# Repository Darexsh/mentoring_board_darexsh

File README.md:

* * *

<div align="center">

🧩 ESP32-S3 Mentoring Board
==========================

**A multi-function mentoring/training board with ESP32-S3, common sensors, inputs, and LEDs**  
🧠🛠️🎛️💡📦

<sub>Check out my bot in Telegram for an easy project overview.<br>If you want to support more projects, you can leave a small donation for a coffee.</sub>

</div>

* * *

✨ Authors
---------

| Name | GitHub | Role | Contact | Contributions |
| --- | --- | --- | --- | --- |
| **[Darexsh by Daniel Sichler](https://github.com/Darexsh)** | [Link](https://github.com/Darexsh?tab=repositories) | Hardware & Firmware Development 🖥️🛠️ | 📧 [E-Mail](mailto:sichler.daniel@gmail.com) | Concept, Hardware, Firmware, Board Bring-up |

* * *

🚀 About the Project
--------------------

This project is a **mentoring/training board** based on the ESP32-S3 microcontroller. It combines common sensors, inputs, LEDs, and storage so embedded features can be demonstrated and tested on a single board.

### 🛠️ Technologies

* **Microcontroller:** ESP32-S3-WROOM-1-N8R8  
* **Sensors:** VCNL4040 (ambient light & proximity), SHT4x (temperature & humidity), BNO085 (IMU), ADS1015 (ADC)  
* **Inputs:** push buttons, tactile switches, potentiometers, joystick, rotary encoder  
* **Outputs:** WS2812B-2020 addressable LEDs  
* **Storage:** microSD card (SPI)  
* **Display:** I2C display header  
* **Software:** C++, Arduino framework (PlatformIO)  
* **Tools:** KiCad, PlatformIO, Git  

* * *

📋 Features
===========

* **🧭 Sensor Demonstrations:** IMU, proximity/light, temperature/humidity, external ADC  
* **🎛️ Input Practice:** buttons, tactile switches, potentiometers, joystick, encoder  
* **💡 LED Control:** WS2812B addressable LEDs  
* **📦 Data Logging:** microSD over SPI  
* **🖥️ Optional I2C Display:** header for showing sensor values  
* **🧩 Modular Firmware:** enable features via compile-time flags  

* * *

🔧 Hardware Setup
-----------------

* **ESP32-S3 module**  
* **VCNL4040, SHT4x, BNO085, ADS1015** on I2C  
* **WS2812B-2020 LED chain**  
* **microSD socket** over SPI  
* **Joystick, potentiometers, buttons, encoder** for user input  
* **I2C display connector**  

* * *

🚀 Installation & Usage
-----------------------

1. Open the KiCad project in `Hardware/` if you want to inspect or modify the hardware.  
2. Build and flash the firmware with PlatformIO:  
   
   ```bash
   cd Software
   pio run -t upload
   pio device monitor
   ```
3. Enable/disable features in `Software/lib/select_sensory/select_sensory.h`.  

* * *

## 📜 License

This project is licensed under the **MIT License**.

This license applies to the updater application code in this repository. Upstream patch and app projects remain under their own licenses and notice terms.

**Copyright (c) 2025 Darexsh by Daniel Sichler**

You are free to use, copy, modify, merge, publish, distribute, sublicense, and sell this software under the terms of the MIT License.

When redistributing this project, you must include the original copyright notice and the MIT License permission notice.

**Developer:** Darexsh by Daniel Sichler.

The full license is available in the [LICENSE](LICENSE) file.

* * *

<!-- Keep this line! Rendered picture of PCB is going to be displayed after Production files are pushed to branch! -->

<div align="center"> <sub>Created with ❤️ by Daniel Sichler</sub> </div>

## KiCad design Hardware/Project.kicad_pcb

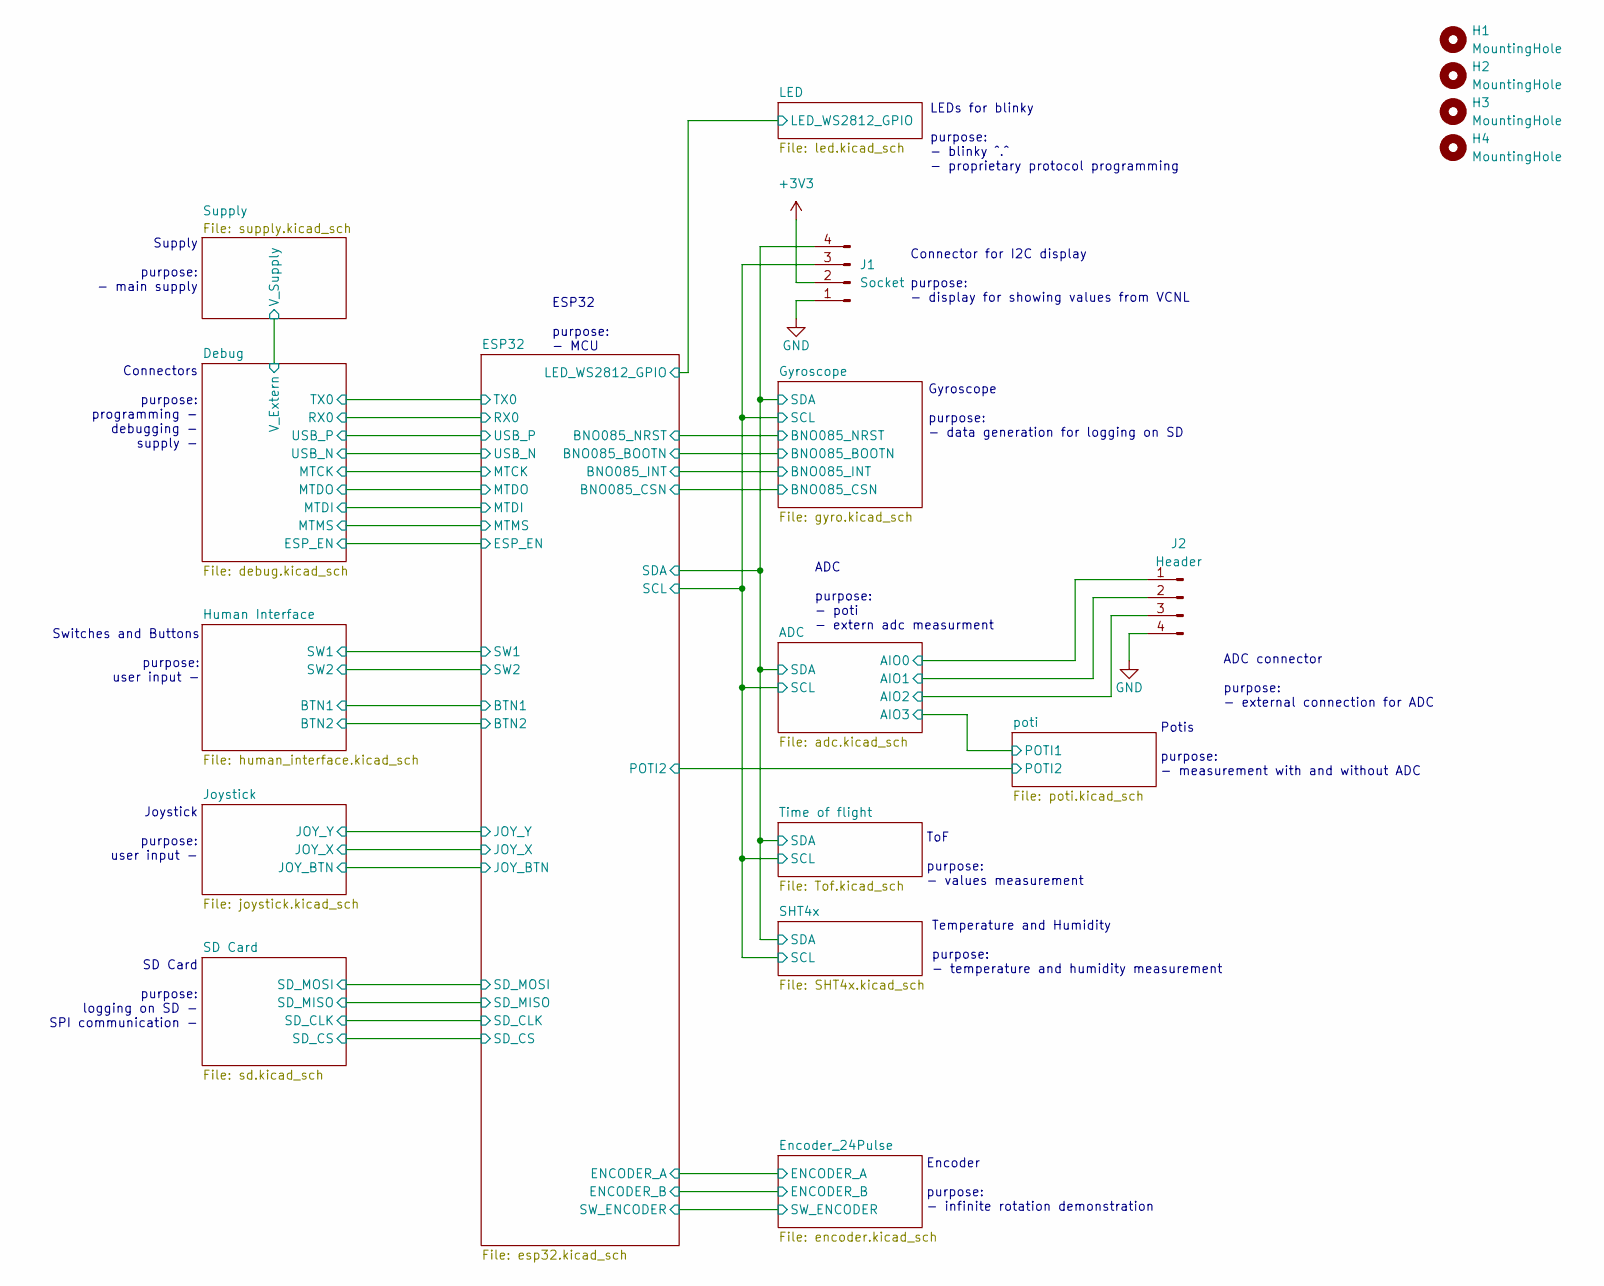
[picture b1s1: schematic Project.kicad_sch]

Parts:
H1, H2, H3, H4: MountingHole; MountingHole_3.2mm_M3
J1: Socket; PinSocket_1x04_P2.54mm_Vertical; LCSC C2718488
J2: Header; PinHeader_1x04_P2.54mm_Vertical; LCSC C2691448

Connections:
+3V3: J1.2; also elsewhere on the board
/ADC/AIO0: J2.1; also elsewhere on the board
/ADC/AIO1: J2.2; also elsewhere on the board
/ADC/AIO2: J2.3; also elsewhere on the board
/ADC/SCL: J1.3; also elsewhere on the board
/ADC/SDA: J1.4; also elsewhere on the board
GND: J1.1, J2.4; also elsewhere on the board

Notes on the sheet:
Connectors purpose: programming - debugging - supply -
Connector for I2C display purpose: - display for showing values from VCNL
ESP32 purpose: - MCU
Temperature and Humidity purpose: - temperature and humidity measurement
Supply purpose: - main supply
Joystick purpose: user input -
SD Card purpose: logging on SD - SPI communication -
ADC connector purpose: - external connection for ADC
Switches and Buttons purpose: user input -
ToF purpose: - values measurement
Potis purpose: - measurement with and without ADC
Gyroscope purpose: - data generation for logging on SD
Encoder purpose: - infinite rotation demonstration
LEDs for blinky purpose: - blinky ^.^ - proprietary protocol programming
ADC purpose: - poti - extern adc measurment

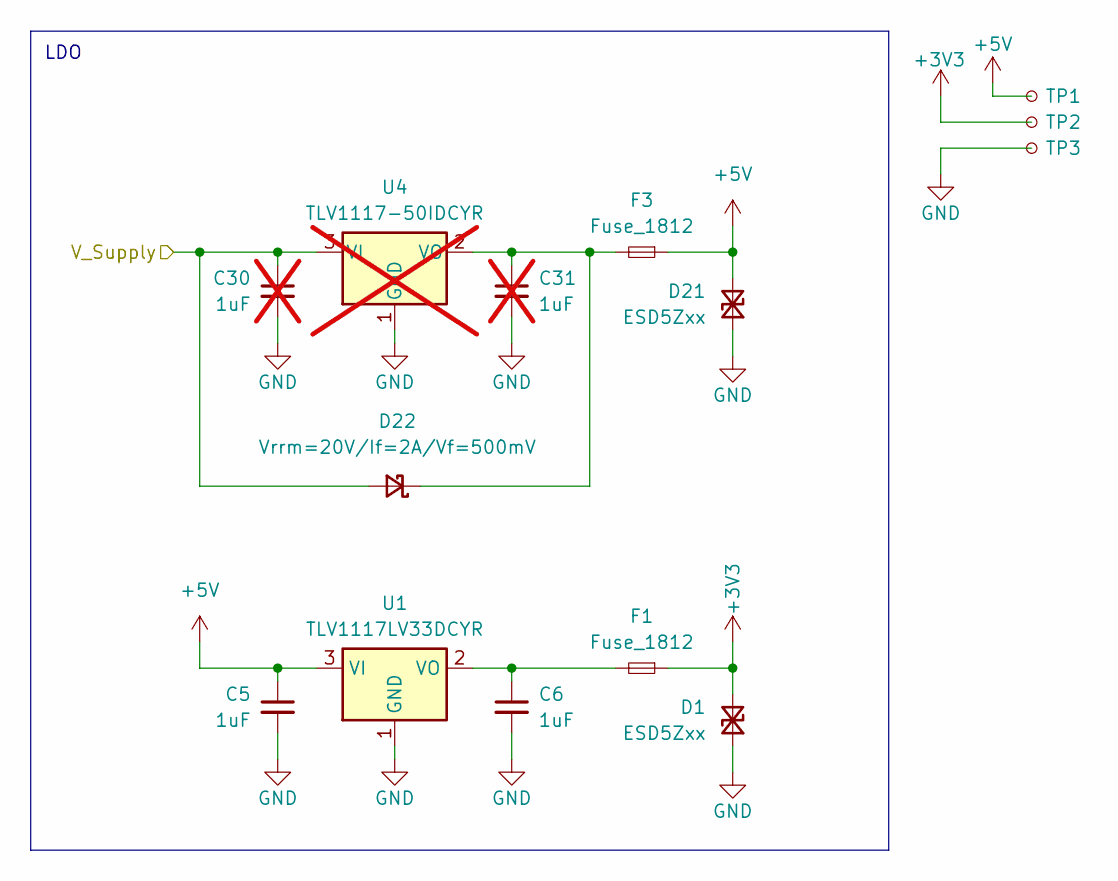
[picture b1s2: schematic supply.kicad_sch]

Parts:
C5, C6: 1uF; C_0603_1608Metric; LCSC C559769
C30, C31: 1uF; C_0603_1608Metric; LCSC C559769; not fitted
D1, D21: ESD5Zxx; D_SOD-523; LCSC C383211
D22: Vrrm=20V/If=2A/Vf=500mV; D_1206_3216Metric; LCSC C143806
F1, F3: Fuse_1812; Fuse_1812_4532Metric; LCSC C883155
TP1, TP2, TP3: TestPoint_Pad_D1.0mm
U1: TLV1117LV33DCYR; SOT-223-3_TabPin2; LCSC C48937499
U4: TLV1117-50IDCYR; SOT-223-3_TabPin2; not fitted

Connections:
+3V3: D1.2 (A2), F1.1, TP2.1; also elsewhere on the board
+5V: C5.1, D21.2 (A2), F3.1, TP1.1, U1.3 (VI); also elsewhere on the board
/Debug/V_Extern: C30.1, D22.2 (A), U4.3 (VI); also elsewhere on the board
GND: C5.2, C6.2, C30.2, C31.2, D1.1 (A1), D21.1 (A1), TP3.1, U1.1 (GND), U4.1 (GND); also elsewhere on the board
unnamed: C31.1, D22.1 (K), F3.2, U4.2 (VO)
unnamed: C6.1, F1.2, U1.2 (VO)

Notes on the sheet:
LDO

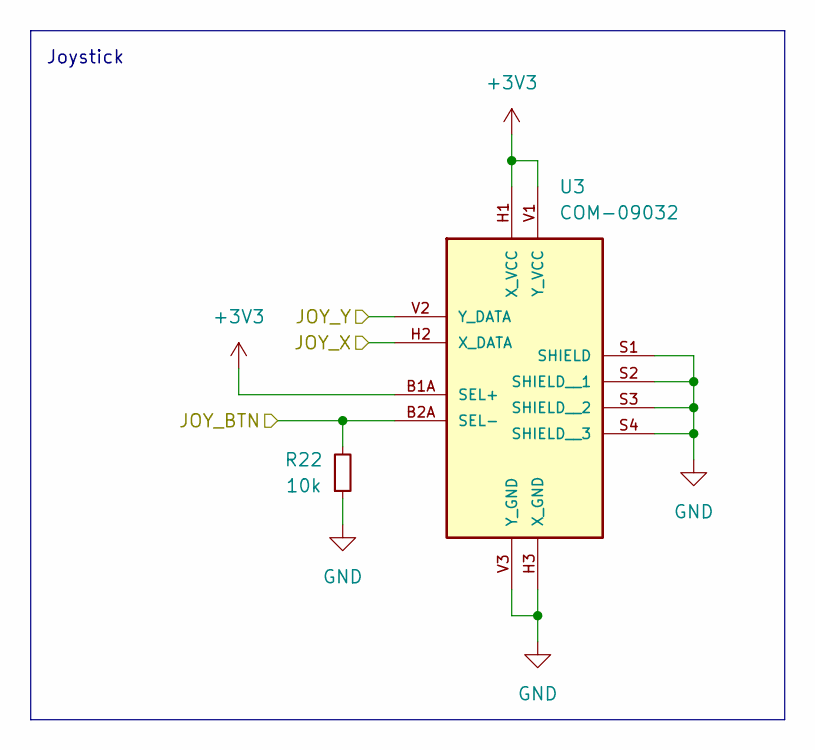
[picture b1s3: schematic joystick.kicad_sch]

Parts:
R22: 10k; R_0603_1608Metric; LCSC C98220
U3: COM-09032

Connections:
+3V3: U3.B1A (SEL+), U3.B1B (SEL+), U3.H1 (X_VCC), U3.V1 (Y_VCC); also elsewhere on the board
/ESP32/JOY_BTN: R22.2, U3.B2A (SEL-), U3.B2B (SEL-); also elsewhere on the board
/ESP32/JOY_X: U3.H2 (X_DATA); also elsewhere on the board
/ESP32/JOY_Y: U3.V2 (Y_DATA); also elsewhere on the board
GND: R22.1, U3.H3 (X_GND), U3.S1 (SHIELD), U3.S2 (SHIELD__1), U3.S3 (SHIELD__2), U3.S4 (SHIELD__3), U3.V3 (Y_GND); also elsewhere on the board

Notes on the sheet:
Joystick

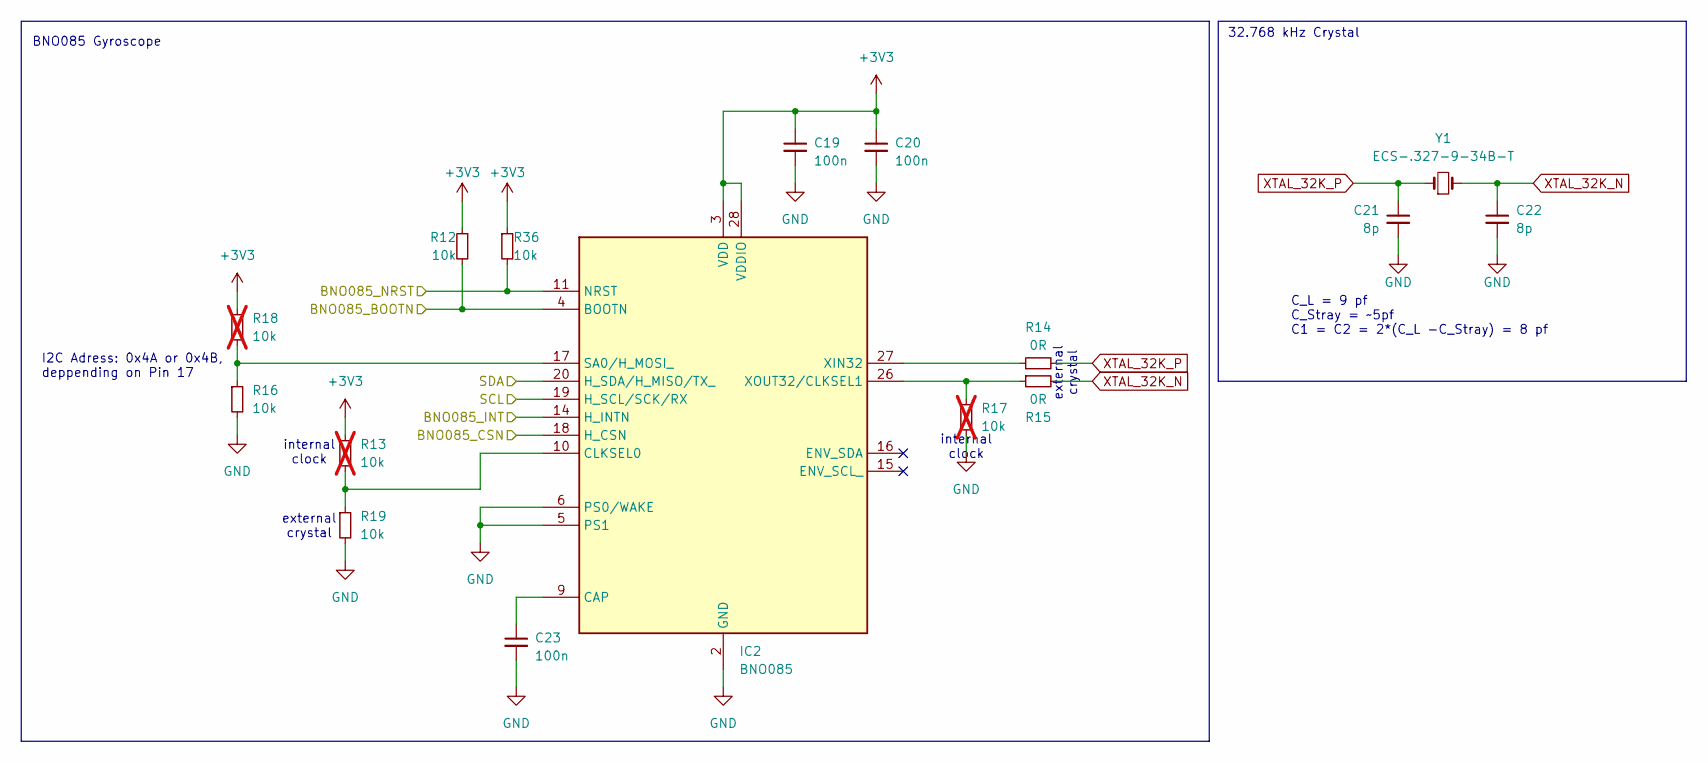
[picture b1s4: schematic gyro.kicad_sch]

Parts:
C19, C20, C23: 100n; C_0603_1608Metric; LCSC C14663
C21, C22: 8p; C_0603_1608Metric
IC2: BNO085
R12, R16, R19, R36: 10k; R_0603_1608Metric; LCSC C98220
R13, R17, R18: 10k; R_0603_1608Metric; LCSC C98220; not fitted
R14, R15: 0R; R_0603_1608Metric; LCSC C95177
Y1: ECS-.327-9-34B-T; LCSC C387600

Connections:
+3V3: C19.1, C20.1, IC2.3 (VDD), IC2.28 (VDDIO), R12.1, R13.1, R18.1, R36.1; also elsewhere on the board
/ADC/SCL: IC2.19 (H_SCL/SCK/RX); also elsewhere on the board
/ADC/SDA: IC2.20 (H_SDA/H_MISO/TX_); also elsewhere on the board
/ESP32/BNO085_BOOTN: IC2.4 (BOOTN), R12.2; also elsewhere on the board
/ESP32/BNO085_CSN: IC2.18 (H_CSN); also elsewhere on the board
/ESP32/BNO085_INT: IC2.14 (H_INTN); also elsewhere on the board
/ESP32/BNO085_NRST: IC2.11 (NRST), R36.2; also elsewhere on the board
GND: C19.2, C20.2, C21.2, C22.2, C23.2, IC2.2 (GND), IC2.5 (PS1), IC2.6 (PS0/WAKE), IC2.25 (GND_2), R16.2, R17.2, R19.2; also elsewhere on the board
unnamed: C23.1, IC2.9 (CAP)
unnamed: IC2.10 (CLKSEL0), R13.2, R19.1
unnamed: IC2.17 (SA0/H_MOSI_), R16.1, R18.2
unnamed: IC2.27 (XIN32), R14.1
unnamed: IC2.26 (XOUT32/CLKSEL1), R15.1, R17.1
XTAL_32K_N: C22.1, R15.2, Y1.2
XTAL_32K_P: C21.1, R14.2, Y1.1

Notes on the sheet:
32.768 kHz Crystal
BNO085 Gyroscope
internal clock
I2C Adress: 0x4A or 0x4B, deppending on Pin 17
external crystal
C_L = 9 pf C_Stray = ~5pf C1 = C2 = 2*(C_L -C_Stray) = 8 pf

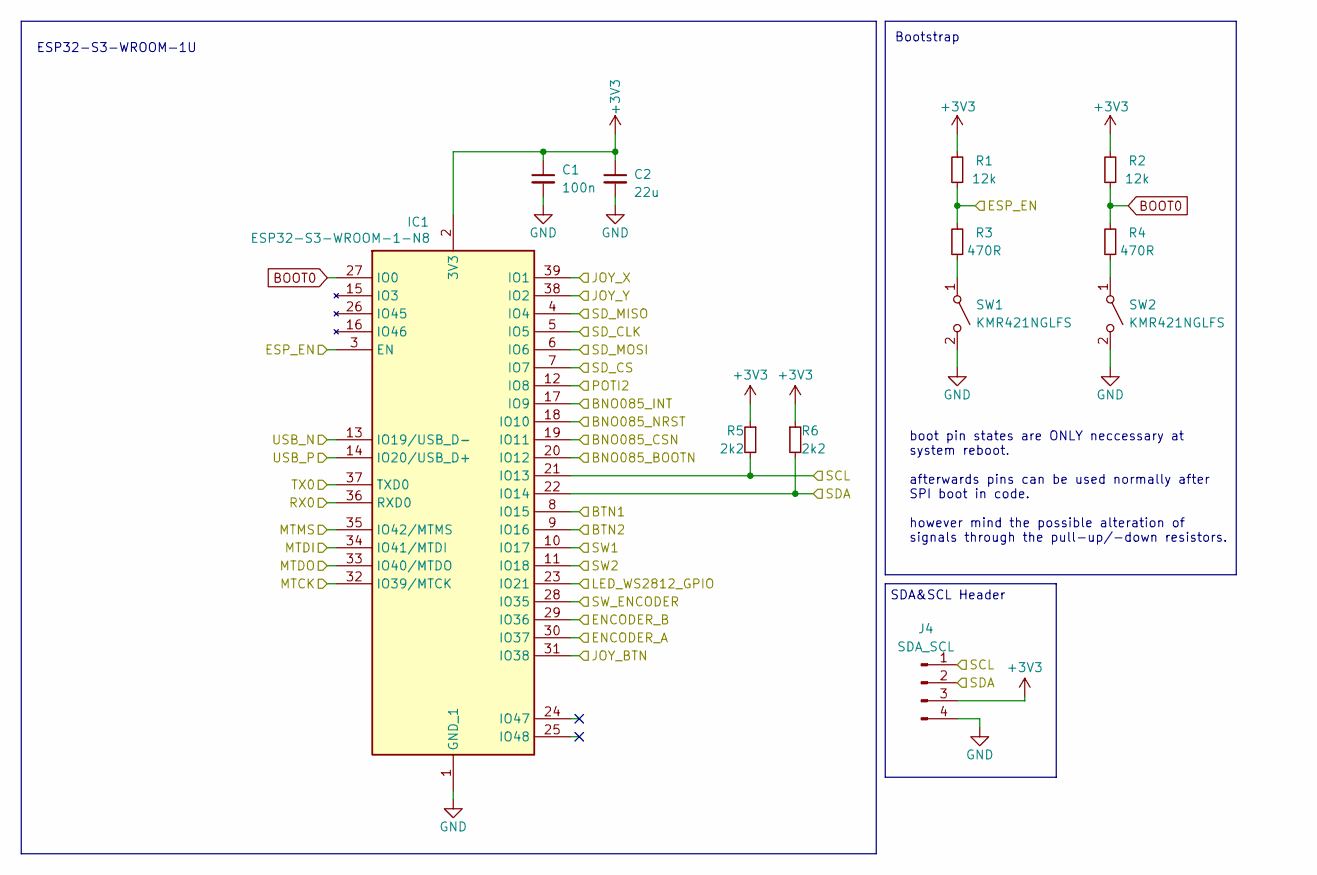
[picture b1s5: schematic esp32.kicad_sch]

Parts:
C1: 100n; C_0603_1608Metric; LCSC C14663
C2: 22u; C_0603_1608Metric; LCSC C109448
IC1: ESP32-S3-WROOM-1-N8; ESP32S3WROOM1N8R8; LCSC C2913198
J4: SDA_SCL; PinHeader_1x04_P2.54mm_Vertical; LCSC C2691448
R1, R2: 12k; R_0603_1608Metric; LCSC C114659
R3, R4: 470R; R_0603_1608Metric; LCSC C114669
R5, R6: 2k2; R_0603_1608Metric; LCSC C114662
SW1, SW2: KMR421NGLFS; LCSC C221687

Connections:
+3V3: C1.1, C2.1, IC1.2 (3V3), J4.3, R1.2, R2.2, R5.1, R6.1; also elsewhere on the board
/ADC/SCL: IC1.21 (IO13), J4.1, R5.2; also elsewhere on the board
/ADC/SDA: IC1.22 (IO14), J4.2, R6.2; also elsewhere on the board
/Debug/ESP_EN: IC1.3 (EN), R1.1, R3.2; also elsewhere on the board
/Debug/MTCK: IC1.32 (IO39/MTCK); also elsewhere on the board
/Debug/MTDI: IC1.34 (IO41/MTDI); also elsewhere on the board
/Debug/MTDO: IC1.33 (IO40/MTDO); also elsewhere on the board
/Debug/MTMS: IC1.35 (IO42/MTMS); also elsewhere on the board
/Debug/RX0: IC1.36 (RXD0); also elsewhere on the board
/Debug/TX0: IC1.37 (TXD0); also elsewhere on the board
/Debug/USB_N: IC1.13 (IO19/USB_D-); also elsewhere on the board
/Debug/USB_P: IC1.14 (IO20/USB_D+); also elsewhere on the board
/ESP32/BNO085_BOOTN: IC1.20 (IO12); also elsewhere on the board
/ESP32/BNO085_CSN: IC1.19 (IO11); also elsewhere on the board
/ESP32/BNO085_INT: IC1.17 (IO9); also elsewhere on the board
/ESP32/BNO085_NRST: IC1.18 (IO10); also elsewhere on the board
/ESP32/BTN1: IC1.8 (IO15); also elsewhere on the board
/ESP32/BTN2: IC1.9 (IO16); also elsewhere on the board
/ESP32/ENCODER_A: IC1.30 (IO37); also elsewhere on the board
/ESP32/ENCODER_B: IC1.29 (IO36); also elsewhere on the board
/ESP32/JOY_BTN: IC1.31 (IO38); also elsewhere on the board
/ESP32/JOY_X: IC1.39 (IO1); also elsewhere on the board
/ESP32/JOY_Y: IC1.38 (IO2); also elsewhere on the board
/ESP32/LED_WS2812_GPIO: IC1.23 (IO21); also elsewhere on the board
/ESP32/POTI2: IC1.12 (IO8); also elsewhere on the board
/ESP32/SD_CLK: IC1.5 (IO5); also elsewhere on the board
/ESP32/SD_CS: IC1.7 (IO7); also elsewhere on the board
/ESP32/SD_MISO: IC1.4 (IO4); also elsewhere on the board
/ESP32/SD_MOSI: IC1.6 (IO6); also elsewhere on the board
/ESP32/SW1: IC1.10 (IO17); also elsewhere on the board
/ESP32/SW2: IC1.11 (IO18); also elsewhere on the board
/ESP32/SW_ENCODER: IC1.28 (IO35); also elsewhere on the board
BOOT0: IC1.27 (IO0), R2.1, R4.2
GND: C1.2, C2.2, IC1.1 (GND_1), IC1.40 (GND_2), IC1.41 (GND_3), IC1.42 (GND_4), IC1.43 (GND_5), IC1.44 (GND_6), IC1.45 (GND_7), IC1.46 (GND_8), IC1.47 (GND_9), IC1.48 (GND_10), IC1.49 (GND_11), J4.4, SW1.2 (B), SW2.2 (B); also elsewhere on the board
unnamed: R3.1, SW1.1 (A)
unnamed: R4.1, SW2.1 (A)

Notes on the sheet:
boot pin states are ONLY neccessary at system reboot. afterwards pins can be used normally after SPI boot in code. however mind the possible alteration of signals through the pull-up/-down resistors.
ESP32-S3-WROOM-1U
Bootstrap
SDA&SCL Header

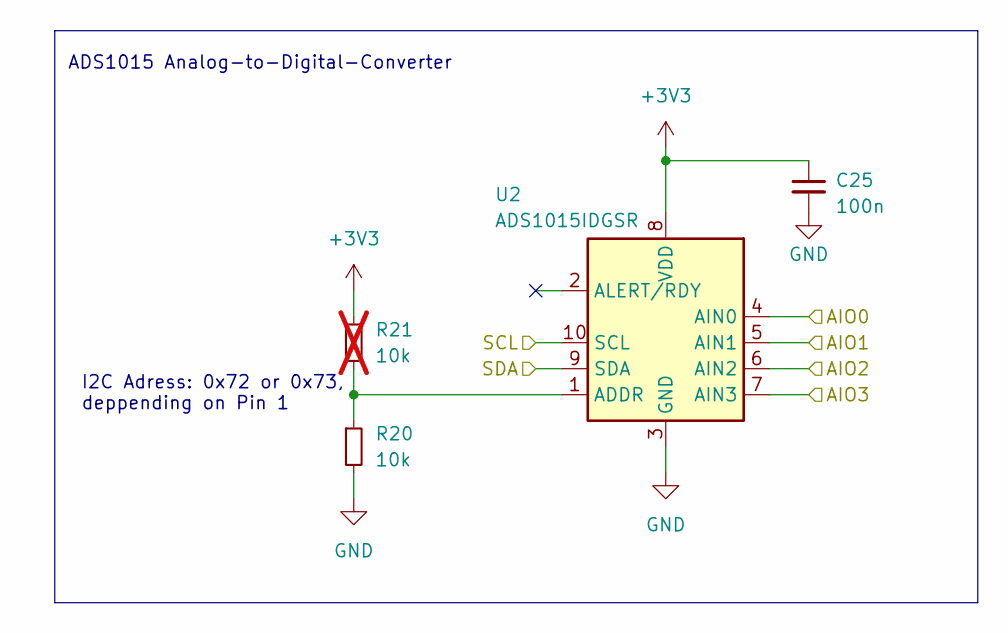
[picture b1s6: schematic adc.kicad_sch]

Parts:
C25: 100n; C_0603_1608Metric; LCSC C14663
R20: 10k; R_0603_1608Metric; LCSC C98220
R21: 10k; R_0603_1608Metric; LCSC C98220; not fitted
U2: ADS1015IDGSR; LCSC C193969

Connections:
+3V3: C25.1, R21.1, U2.8 (VDD); also elsewhere on the board
/ADC/AIO0: U2.4 (AIN0); also elsewhere on the board
/ADC/AIO1: U2.5 (AIN1); also elsewhere on the board
/ADC/AIO2: U2.6 (AIN2); also elsewhere on the board
/ADC/AIO3: U2.7 (AIN3); also elsewhere on the board
/ADC/SCL: U2.10 (SCL); also elsewhere on the board
/ADC/SDA: U2.9 (SDA); also elsewhere on the board
GND: C25.2, R20.2, U2.3 (GND); also elsewhere on the board
unnamed: R20.1, R21.2, U2.1 (ADDR)

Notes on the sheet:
ADS1015 Analog-to-Digital-Converter
I2C Adress: 0x72 or 0x73, deppending on Pin 1

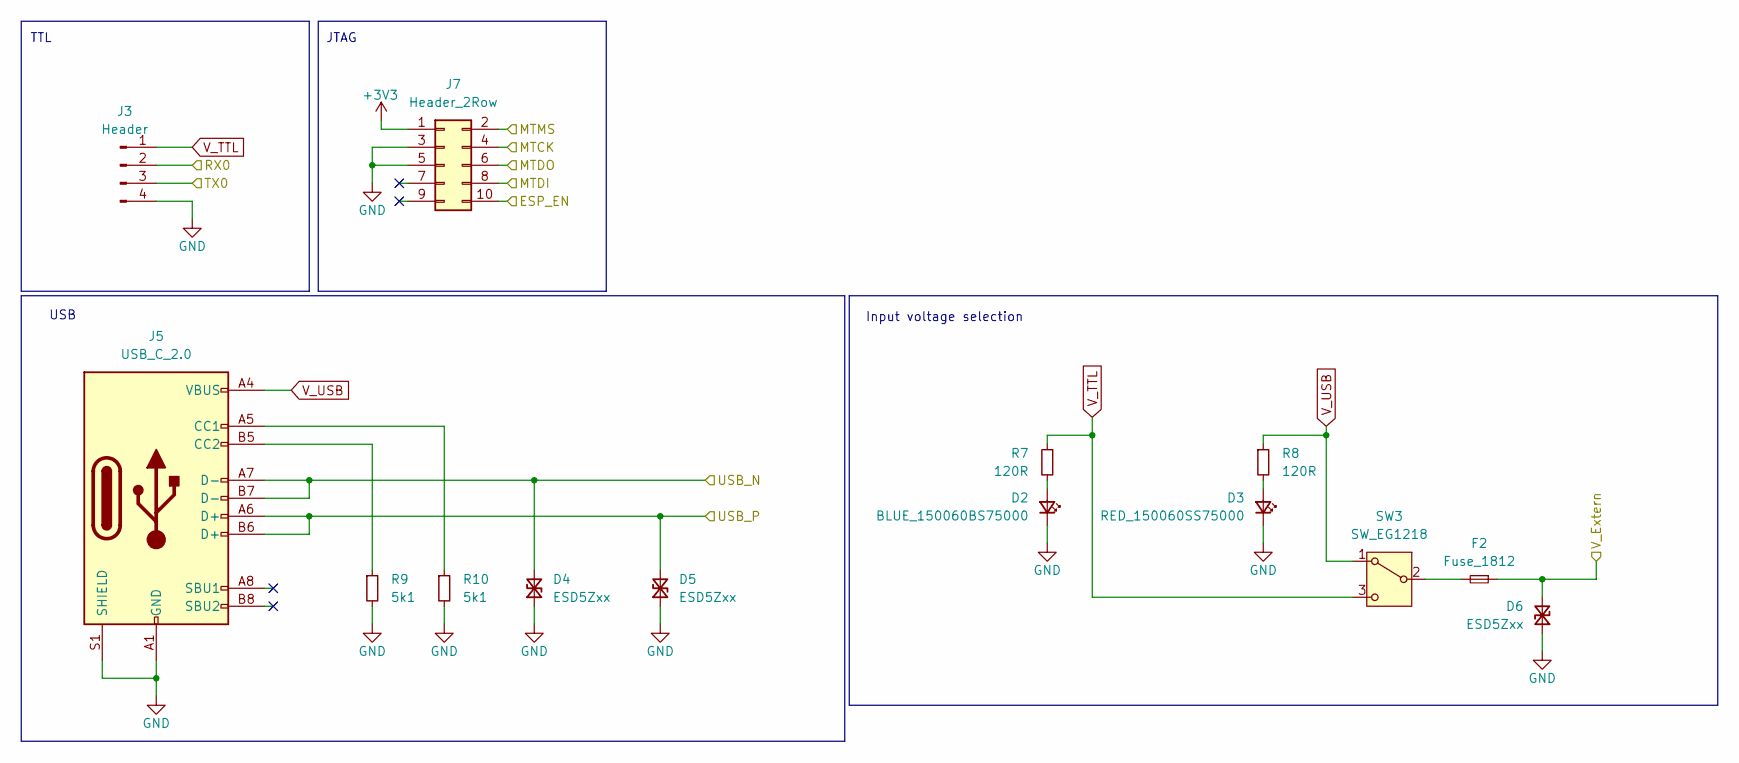
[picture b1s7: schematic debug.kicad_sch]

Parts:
D2: BLUE_150060BS75000; D_0603_1608Metric; LCSC C965807
D3: RED_150060SS75000; D_0603_1608Metric; LCSC C965799
D4, D5, D6: ESD5Zxx; D_SOD-523; LCSC C383211
F2: Fuse_1812; Fuse_1812_4532Metric; LCSC C883155
J3: Header; PinHeader_1x04_P2.54mm_Vertical; LCSC C2691448
J5: USB_C_2.0; USB-C; LCSC C5117882
J7: Header_2Row; PinHeader_2x05_P1.27mm_Vertical; LCSC C7501289
R7, R8: 120R; R_0603_1608Metric; LCSC C114640
R9, R10: 5k1; R_0603_1608Metric; LCSC C105580
SW3: SW_EG1218; EG1218; LCSC C2848901

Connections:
+3V3: J7.1; also elsewhere on the board
/Debug/ESP_EN: J7.10; also elsewhere on the board
/Debug/MTCK: J7.4; also elsewhere on the board
/Debug/MTDI: J7.8; also elsewhere on the board
/Debug/MTDO: J7.6; also elsewhere on the board
/Debug/MTMS: J7.2; also elsewhere on the board
/Debug/RX0: J3.2; also elsewhere on the board
/Debug/TX0: J3.3; also elsewhere on the board
/Debug/USB_N: D4.2 (A2), J5.A7 (D-), J5.B7 (D-); also elsewhere on the board
/Debug/USB_P: D5.2 (A2), J5.A6 (D+), J5.B6 (D+); also elsewhere on the board
/Debug/V_Extern: D6.2 (A2), F2.1; also elsewhere on the board
GND: D2.1 (K), D3.1 (K), D4.1 (A1), D5.1 (A1), D6.1 (A1), J3.4, J5.A1 (GND), J5.A12 (GND), J5.S1 (SHIELD), J7.3, J7.5, R9.2, R10.2; also elsewhere on the board
unnamed: D2.2 (A), R7.2
unnamed: D3.2 (A), R8.2
unnamed: J5.A5 (CC1), R10.1
unnamed: J5.B5 (CC2), R9.1
unnamed: F2.2, SW3.2 (B)
V_TTL: J3.1, R7.1, SW3.3 (C)
V_USB: J5.A4 (VBUS), J5.A9 (VBUS), R8.1, SW3.1 (A)

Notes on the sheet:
USB
JTAG
TTL
Input voltage selection

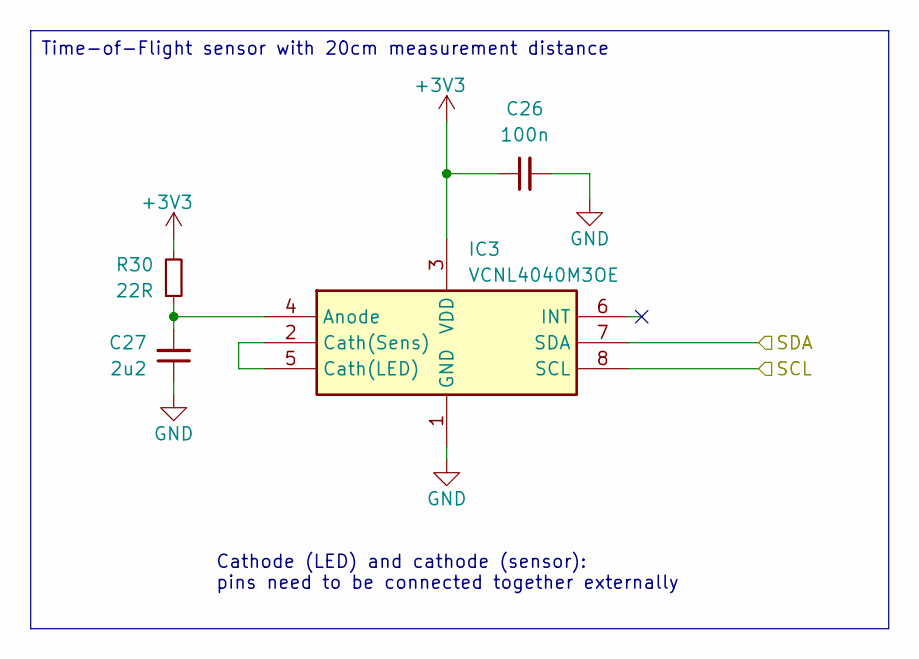
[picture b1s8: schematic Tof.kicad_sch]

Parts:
C26: 100n; C_0603_1608Metric; LCSC C14663
C27: 2u2; C_0603_1608Metric; LCSC C309478
IC3: VCNL4040M3OE; LCSC C142526
R30: 22R; R_0603_1608Metric; LCSC C107701

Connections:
+3V3: C26.1, IC3.3 (VDD), R30.2; also elsewhere on the board
/ADC/SCL: IC3.8 (SCL); also elsewhere on the board
/ADC/SDA: IC3.7 (SDA); also elsewhere on the board
GND: C26.2, C27.1, IC3.1 (GND); also elsewhere on the board
unnamed: C27.2, IC3.4 (Anode), R30.1
unnamed: IC3.2 (Cath(Sens)), IC3.5 (Cath(LED))

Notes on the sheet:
Cathode (LED) and cathode (sensor): pins need to be connected together externally
Time-of-Flight sensor with 20cm measurement distance

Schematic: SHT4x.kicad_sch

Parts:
C3: 100n; C_0603_1608Metric; LCSC C14663
U5: SHT4x; Sensirion_DFN-4_1.5x1.5mm_P0.8mm_SHT4x_NoCentralPad

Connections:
+3V3: C3.2, U5.3 (VDD); also elsewhere on the board
/ADC/SCL: U5.2 (SCL); also elsewhere on the board
/ADC/SDA: U5.1 (SDA); also elsewhere on the board
GND: C3.1, U5.4 (VSS); also elsewhere on the board

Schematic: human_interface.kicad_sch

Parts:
D19, D20: GREEN_150060SS75000; D_0603_1608Metric; LCSC C19171301
R23, R24: 10k; R_0603_1608Metric; LCSC C98220
R25, R28: 120R; R_0603_1608Metric; LCSC C114640
R26, R27: 470R; R_0603_1608Metric; LCSC C114669
SW4, SW5: SW_EG1218; EG1218; LCSC C2848901
SW6, SW7: BTN_TL3305; SW_SPST_TL3305A; LCSC C410371

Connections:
+3V3: R23.2, R24.2, R26.2, R27.2; also elsewhere on the board
/ESP32/BTN1: R25.1, SW6.2 (B); also elsewhere on the board
/ESP32/BTN2: R28.1, SW7.2 (B); also elsewhere on the board
/ESP32/SW1: SW4.2 (B); also elsewhere on the board
/ESP32/SW2: SW5.2 (B); also elsewhere on the board
GND: D19.1 (K), D20.1 (K), SW4.1 (A), SW5.1 (A); also elsewhere on the board
unnamed: D19.2 (A), R25.2
unnamed: D20.2 (A), R28.2
unnamed: R23.1, SW4.3 (C)
unnamed: R24.1, SW5.3 (C)
unnamed: R27.1, SW6.1 (A)
unnamed: R26.1, SW7.1 (A)

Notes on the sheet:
Push Buttons (LED: On@1, Off@0)
Tactile Switches

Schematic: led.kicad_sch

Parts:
C7, C8, C9, C10, C11, C12, C13, C14, C15, C16, C17, C18: 100n; C_0603_1608Metric; LCSC C14663; not fitted
D7, D8, D9, D10, D11, D12, D13, D14, D15, D16, D17, D18: WS2812B-2020; LED_WS2812B-2020_PLCC4_2.0x2.0mm; LCSC C965555
R11: 330R; R_0603_1608Metric; LCSC C105881

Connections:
+5V: C7.1, C8.1, C9.1, C10.1, C11.1, C12.1, C13.1, C14.1, C15.1, C16.1, C17.1, C18.1, D7.4 (VDD), D8.4 (VDD), D9.4 (VDD), D10.4 (VDD), D11.4 (VDD), D12.4 (VDD), D13.4 (VDD), D14.4 (VDD), D15.4 (VDD), D16.4 (VDD), D17.4 (VDD), D18.4 (VDD); also elsewhere on the board
/ESP32/LED_WS2812_GPIO: R11.1; also elsewhere on the board
GND: C7.2, C8.2, C9.2, C10.2, C11.2, C12.2, C13.2, C14.2, C15.2, C16.2, C17.2, C18.2, D7.2 (VSS), D8.2 (VSS), D9.2 (VSS), D10.2 (VSS), D11.2 (VSS), D12.2 (VSS), D13.2 (VSS), D14.2 (VSS), D15.2 (VSS), D16.2 (VSS), D17.2 (VSS), D18.2 (VSS); also elsewhere on the board
unnamed: D7.3 (DIN), R11.2
unnamed: D7.1 (DOUT), D8.3 (DIN)
unnamed: D8.1 (DOUT), D9.3 (DIN)
unnamed: D9.1 (DOUT), D10.3 (DIN)
unnamed: D10.1 (DOUT), D11.3 (DIN)
unnamed: D11.1 (DOUT), D12.3 (DIN)
unnamed: D12.1 (DOUT), D13.3 (DIN)
unnamed: D13.1 (DOUT), D14.3 (DIN)
unnamed: D14.1 (DOUT), D15.3 (DIN)
unnamed: D15.1 (DOUT), D16.3 (DIN)
unnamed: D16.1 (DOUT), D17.3 (DIN)
unnamed: D17.1 (DOUT), D18.3 (DIN)

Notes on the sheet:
WS2812B-2020 LEDs

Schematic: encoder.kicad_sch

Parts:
C28, C29: 100n; C_0603_1608Metric; LCSC C14663
IC4: PEC12R-4220F-S0024; PEC12R4220FS0024; LCSC C18164805
JP3, JP4: SolderJumper-2_P1.3mm_Open_TrianglePad1.0x1.5mm
R31, R32, R33, R34, R35: 10k; R_0603_1608Metric; LCSC C98220

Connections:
+3V3: R31.1, R32.1, R33.1; also elsewhere on the board
/ESP32/ENCODER_A: C29.1, JP3.1 (A), R34.2; also elsewhere on the board
/ESP32/ENCODER_B: C28.1, JP4.2 (B), R35.2; also elsewhere on the board
/ESP32/SW_ENCODER: IC4.2, R33.2; also elsewhere on the board
GND: C28.2, C29.2, IC4.1, IC4.C1, IC4.MH1, IC4.MH2; also elsewhere on the board
unnamed: IC4.A1, JP3.2 (B), R31.2, R34.1
unnamed: IC4.B1, JP4.1 (A), R32.2, R35.1

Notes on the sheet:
Encoder with 24 positions
Filter circuit Close JP3 and JP4, omit R31-R32, R34-R35 and C28-C29 to completely bypass the filter circuit.

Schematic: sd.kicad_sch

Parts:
C24: 100n; C_0603_1608Metric; LCSC C14663
J6: Micro_SD_Card; MSD1A; LCSC C393941

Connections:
+3V3: C24.1, J6.4 (VDD); also elsewhere on the board
/ESP32/SD_CLK: J6.5 (CLK); also elsewhere on the board
/ESP32/SD_CS: J6.2 (DAT3/CD); also elsewhere on the board
/ESP32/SD_MISO: J6.7 (DAT0); also elsewhere on the board
/ESP32/SD_MOSI: J6.3 (CMD); also elsewhere on the board
GND: C24.2, J6.6 (VSS), J6.9 (SHIELD); also elsewhere on the board

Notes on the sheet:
Micro SD-Card reader

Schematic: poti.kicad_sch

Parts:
RV1, RV2: Pot_50k; Potentiometer_Bourns_PTV09A-1_Single_Vertical; LCSC C5357831

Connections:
+3V3: RV1.1, RV2.1; also elsewhere on the board
/ADC/AIO3: RV1.2; also elsewhere on the board
/ESP32/POTI2: RV2.2; also elsewhere on the board
GND: RV1.3, RV2.3; also elsewhere on the board

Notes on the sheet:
Poti 10K

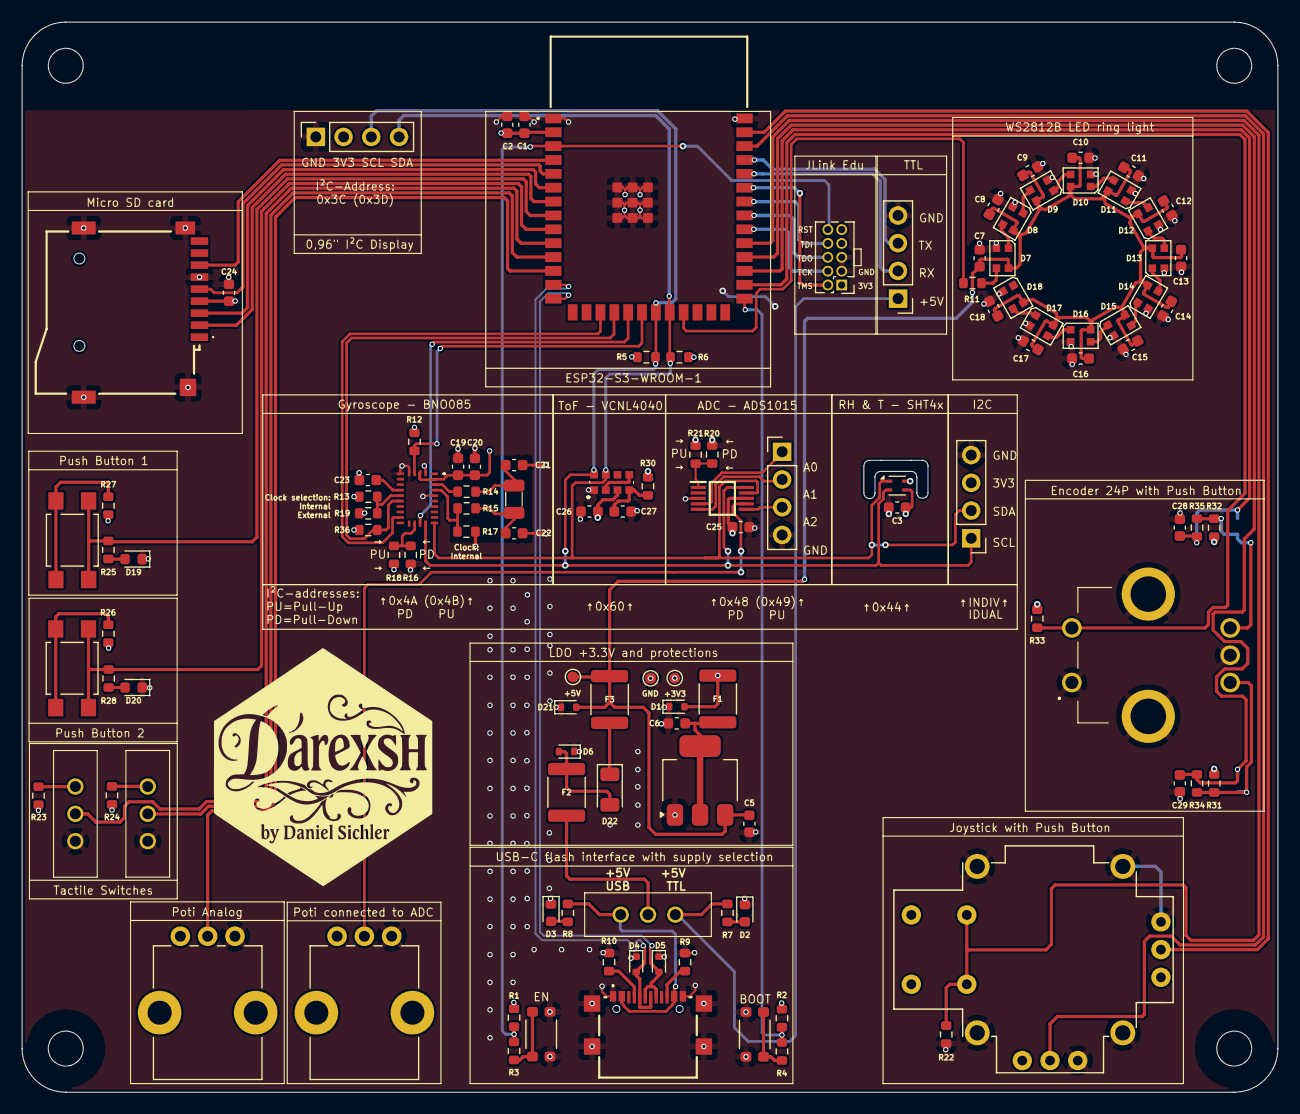
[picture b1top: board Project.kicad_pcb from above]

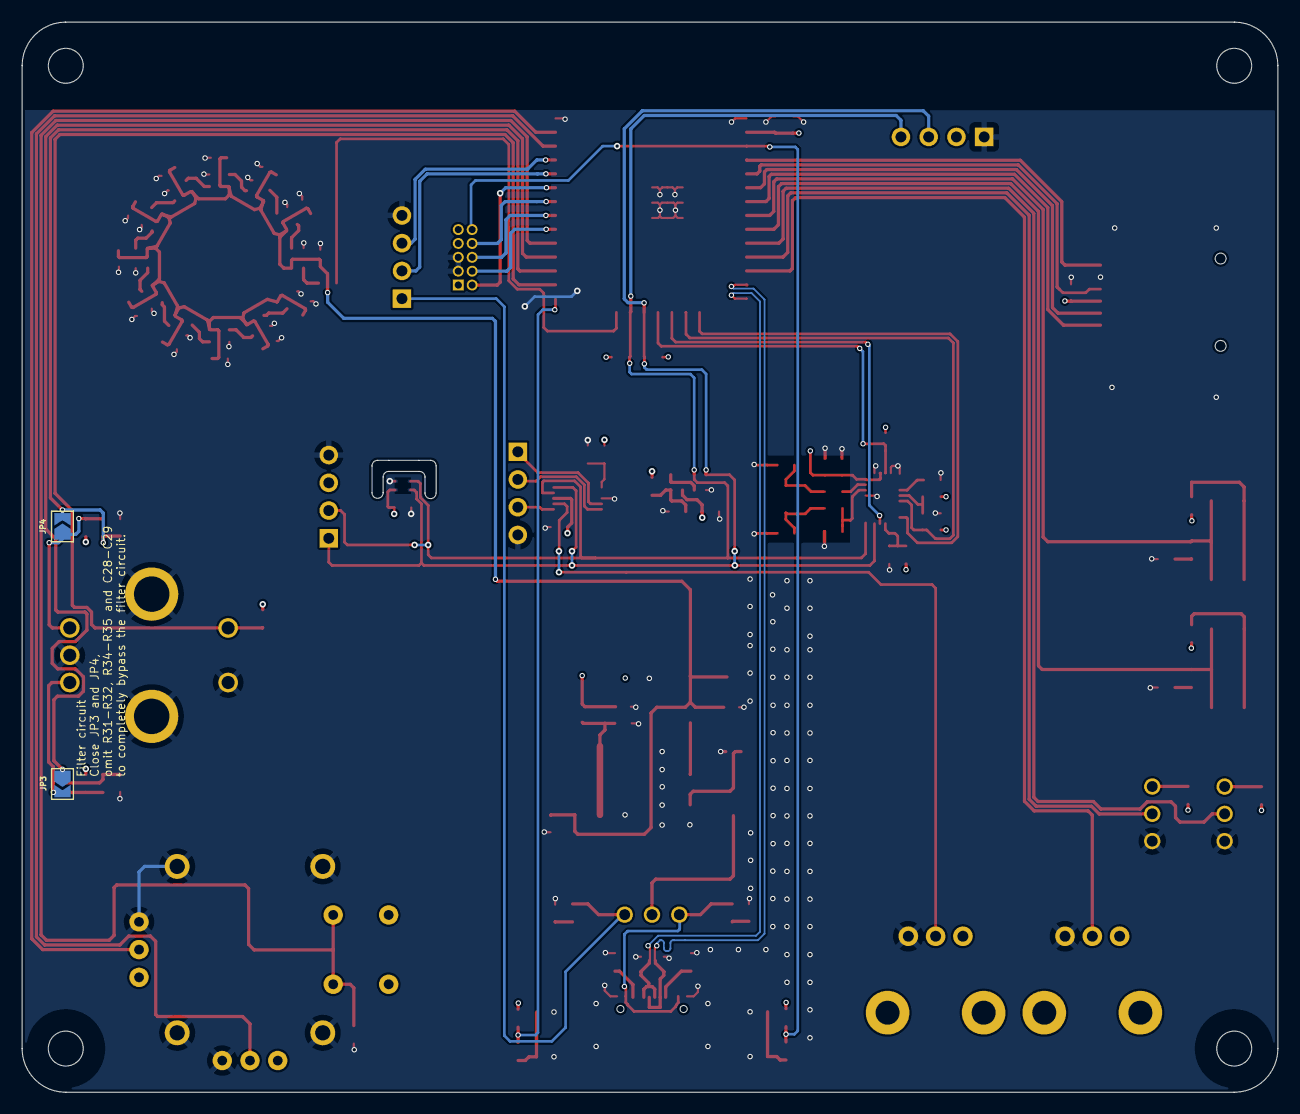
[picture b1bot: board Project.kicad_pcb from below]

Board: 4 copper layers, 115.0 x 98.0 mm, 122 parts (2 on the bottom side), 81 nets.

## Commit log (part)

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2026-02-02 Updated project and README
2026-03-18 Enhance README with Telegram bot and donation info
    Added a Telegram bot badge and donation link to README.
